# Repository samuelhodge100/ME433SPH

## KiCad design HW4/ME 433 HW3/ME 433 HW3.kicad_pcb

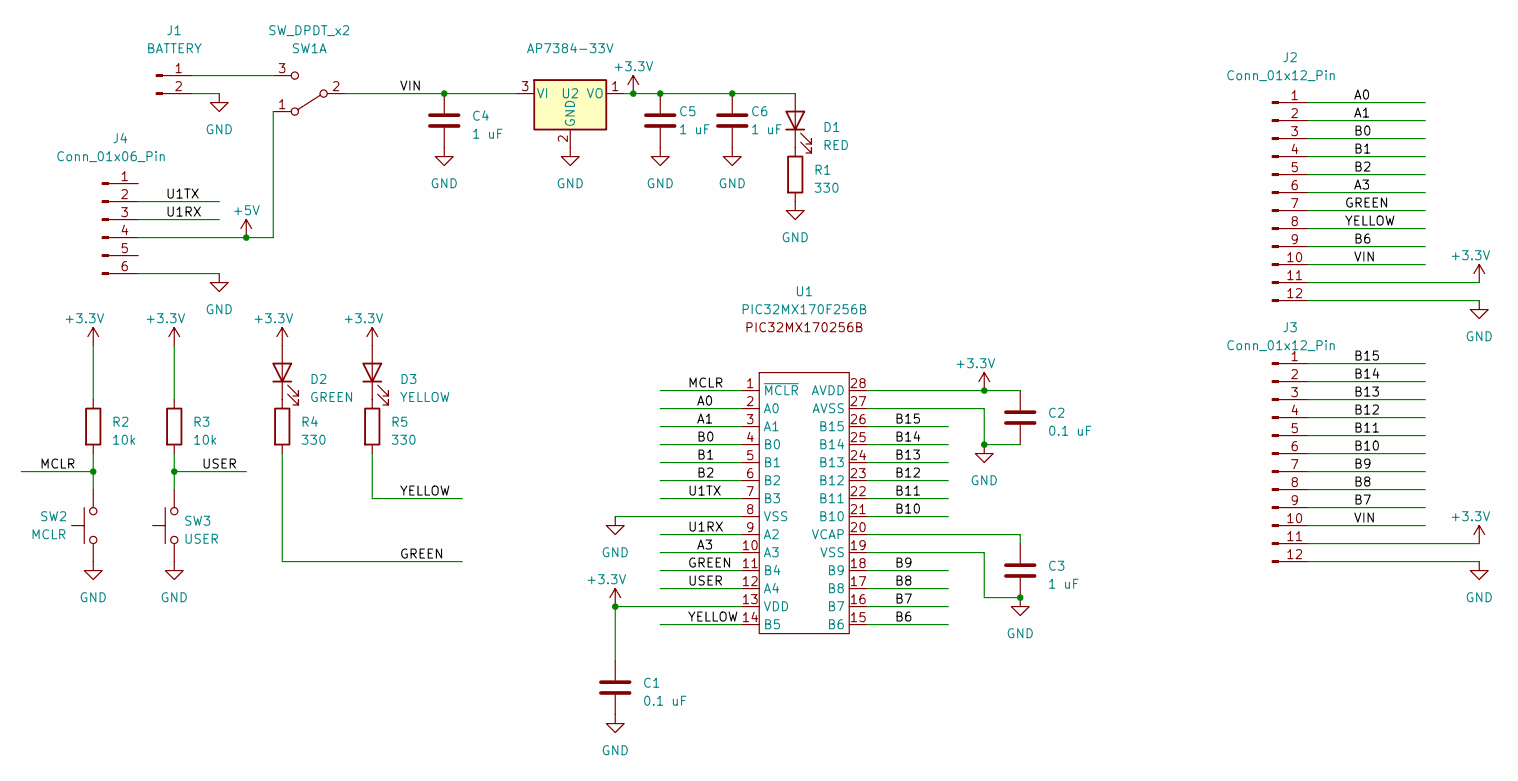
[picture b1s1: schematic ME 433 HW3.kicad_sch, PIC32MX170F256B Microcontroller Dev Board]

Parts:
C1, C2: 0.1 uF; C_Disc_D3.8mm_W2.6mm_P2.50mm
C3, C4, C5, C6: 1 uF; C_Disc_D3.8mm_W2.6mm_P2.50mm
D1: RED; LED_D3.0mm
D2: GREEN; LED_D3.0mm
D3: YELLOW; LED_D3.0mm
J1: BATTERY; PinSocket_1x02_P2.54mm_Vertical
J2, J3: Conn_01x12_Pin; PinSocket_1x12_P2.54mm_Vertical
J4: Conn_01x06_Pin; PinSocket_1x06_P2.54mm_Vertical
R1, R4, R5: 330; R_Axial_DIN0207_L6.3mm_D2.5mm_P7.62mm_Horizontal
R2, R3: 10k; R_Axial_DIN0207_L6.3mm_D2.5mm_P7.62mm_Horizontal
SW1: SW_DPDT_x2; slideswitch
SW2: MCLR; push_button
SW3: USER; push_button
U1: PIC32MX170F256B; DIP-28_W7.62mm_Socket
U2: AP7384-33V; TO-92L_Inline

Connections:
+3.3V: C1.1, C2.1, C5.1, C6.1, D1.2 (A), D2.2 (A), D3.2 (A), J2.11, J3.11, R2.1, R3.1, U1.13 (VDD), U1.28 (AVDD), U2.1 (VO)
+5V: J4.4, SW1.1 (A)
/A0: J2.1, U1.2 (A0)
/A1: J2.2, U1.3 (A1)
/A3: J2.6, U1.10 (A3)
/B0: J2.3, U1.4 (B0)
/B1: J2.4, U1.5 (B1)
/B2: J2.5, U1.6 (B2)
/B6: J2.9, U1.15 (B6)
/B7: J3.9, U1.16 (B7)
/B8: J3.8, U1.17 (B8)
/B9: J3.7, U1.18 (B9)
/B10: J3.6, U1.21 (B10)
/B11: J3.5, U1.22 (B11)
/B12: J3.4, U1.23 (B12)
/B13: J3.3, U1.24 (B13)
/B14: J3.2, U1.25 (B14)
/B15: J3.1, U1.26 (B15)
/GREEN: J2.7, R4.2, U1.11 (B4)
/MCLR: R2.2, SW2.2, U1.1 (~MCLR)
/U1RX: J4.3, U1.9 (A2)
/U1TX: J4.2, U1.7 (B3)
/USER: R3.2, SW3.2, U1.12 (A4)
/VIN: C4.1, J2.10, J3.10, SW1.2 (B), U2.3 (VI)
/YELLOW: J2.8, R5.2, U1.14 (B5)
GND: C1.2, C2.2, C3.2, C4.2, C5.2, C6.2, J1.2, J2.12, J3.12, J4.6, R1.2, SW2.1, SW3.1, U1.8 (VSS), U1.19 (VSS), U1.27 (AVSS), U2.2 (GND)
unnamed: D1.1 (K), R1.1
unnamed: D2.1 (K), R4.1
unnamed: D3.1 (K), R5.1
unnamed: J1.1, SW1.3 (C)
unnamed: C3.1, U1.20 (VCAP)

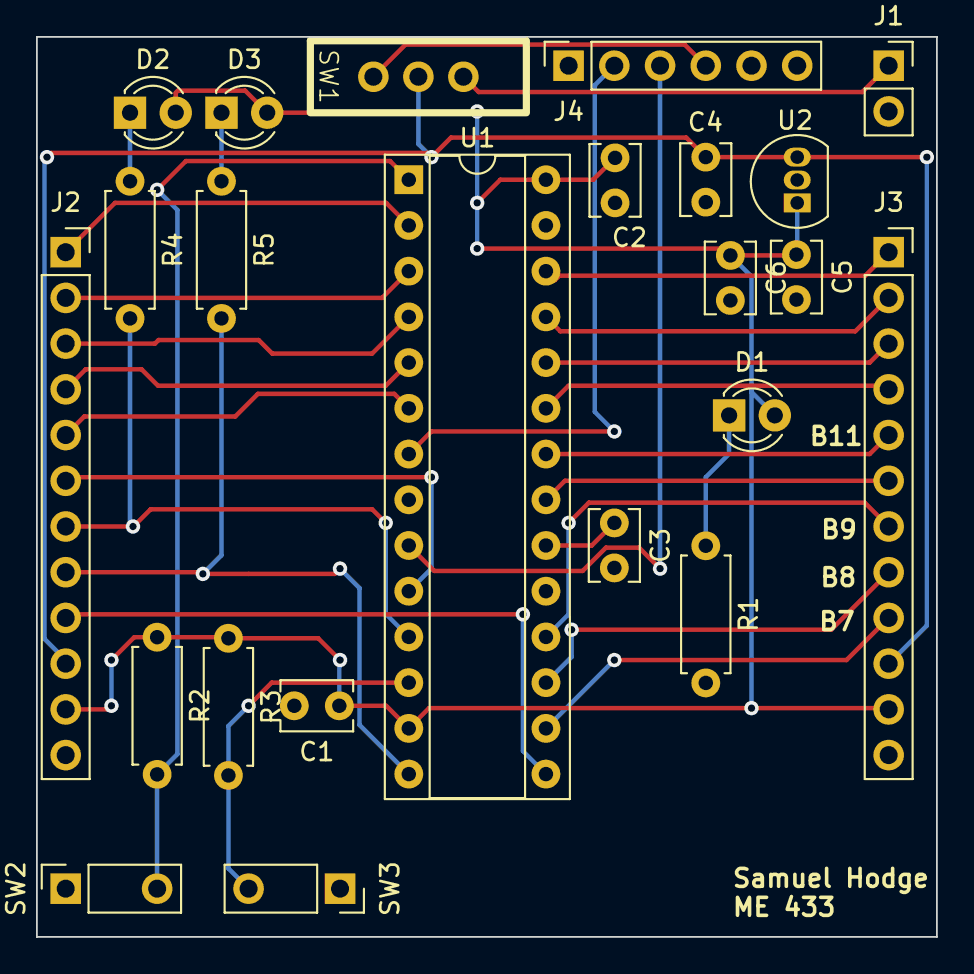
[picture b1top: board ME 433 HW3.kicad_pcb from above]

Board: 2 copper layers, 50.0 x 50.0 mm, 23 parts (0 on the bottom side), 31 nets.

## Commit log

2023-04-02 HW2 commit
2023-04-06 HW3 Code
2023-04-25 HW 5 Code
2023-05-11 HW10
2023-05-16 HW 9
2023-05-16 HW 11
2023-05-30 HW 13 Motor Control
2023-06-07 HW 15
